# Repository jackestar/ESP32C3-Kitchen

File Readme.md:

<div align="center">
<h3>ESP32C3-Kitchen</h3>
<!--  -->
</div>

---

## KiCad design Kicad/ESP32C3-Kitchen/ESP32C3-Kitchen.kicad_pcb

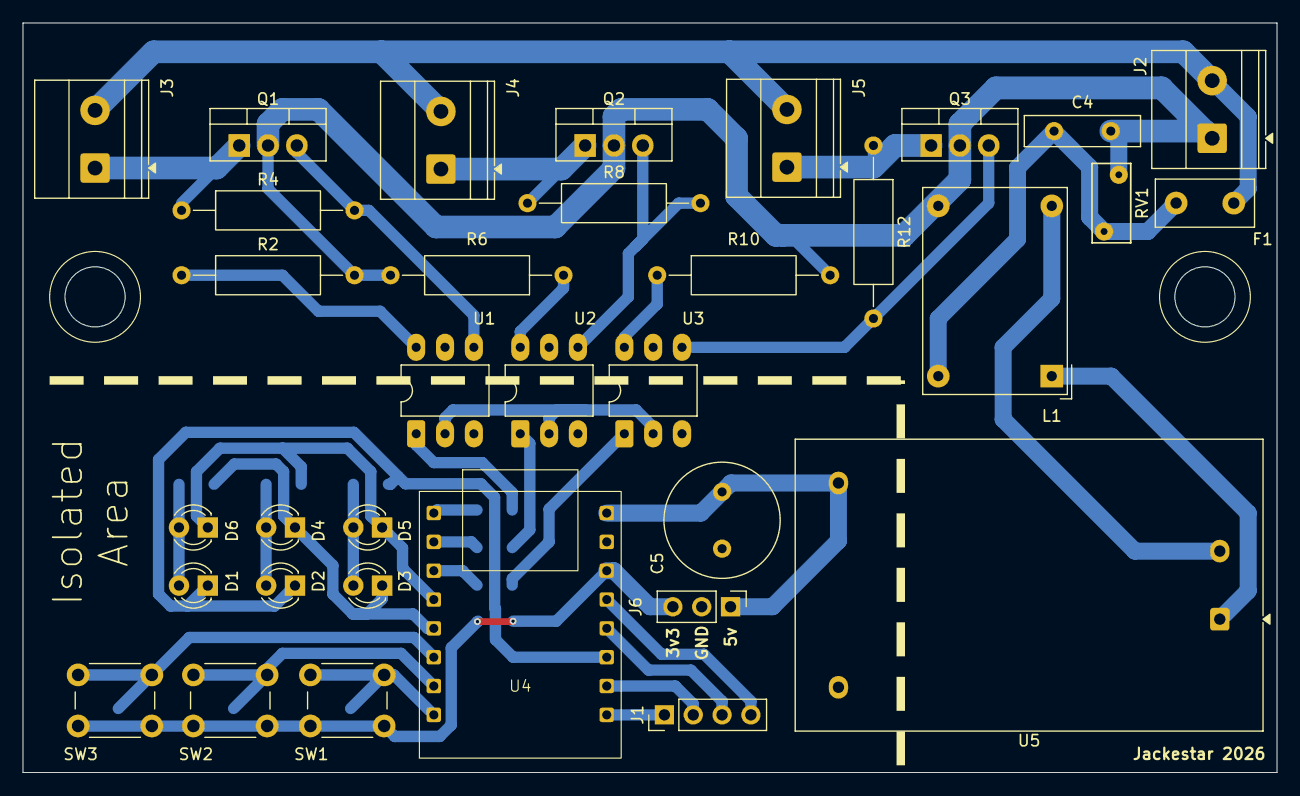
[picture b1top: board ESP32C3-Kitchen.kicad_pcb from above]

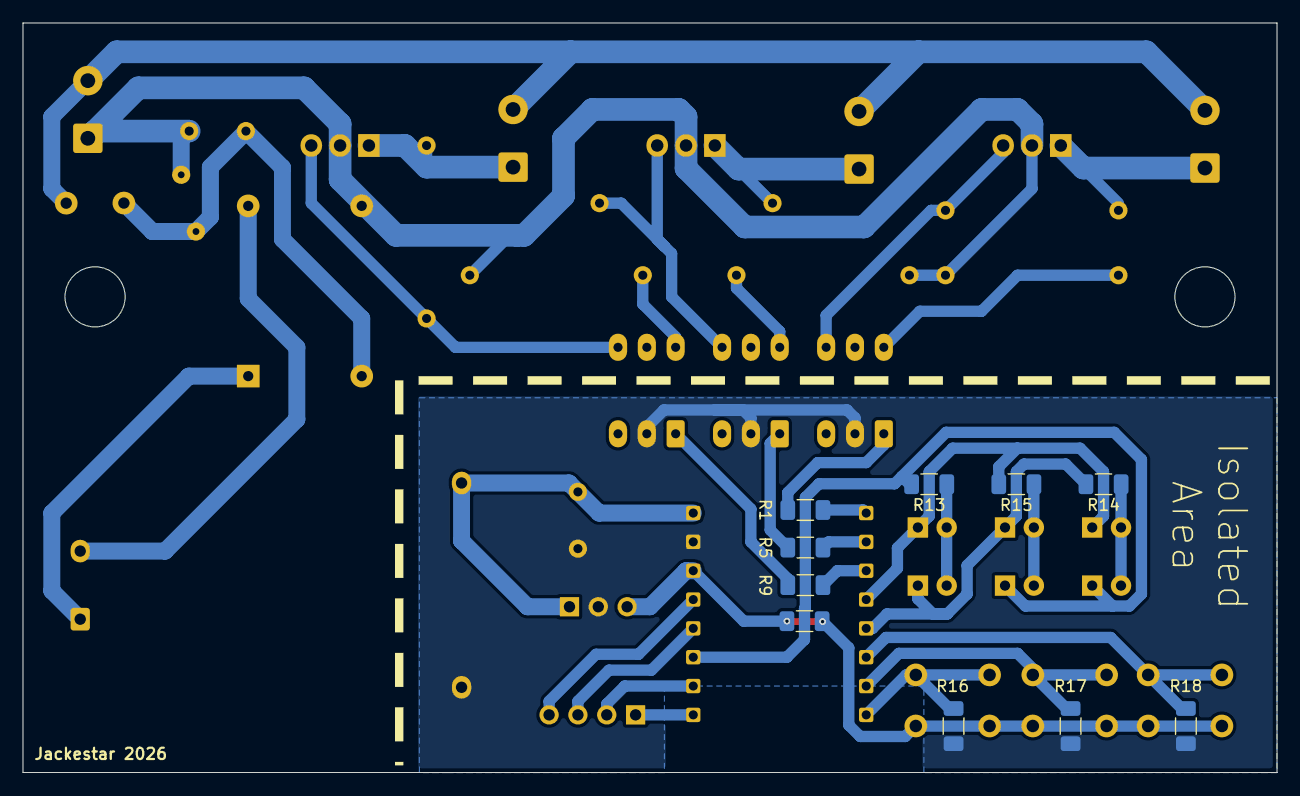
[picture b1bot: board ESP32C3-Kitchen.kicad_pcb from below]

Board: 2 copper layers, 110.5 x 66.0 mm, 43 parts (9 on the bottom side), 36 nets.

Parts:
C4: 0.1u; C_Disc_D10.0mm_W2.5mm_P5.00mm
C5: 220u; C_Radial_D10.0mm_H12.5mm_P5.00mm
D1, D2, D3, D4, D5, D6: LED; LED_D3.0mm
F1: 0.5; Fuse_Littelfuse_395Series
J1: Sense; PinHeader_1x04_P2.54mm_Vertical
J2, J3, J4, J5: Main AC; TerminalBlock_Phoenix_MKDS-1,5-2-5.08_1x02_P5.08mm_Horizont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
J6: Voltage Output; PinHeader_1x03_P2.54mm_Vertical
L1: 10u; Choke_Schaffner_RN212-04-12.5x18.0mm
Q1, Q2, Q3: BTA24-800B; TO-220-3_Vertical
R1, R5, R9: 150; R_1206_3216Metric_Pad1.30x1.75mm_HandSolder
R2, R6, R10: 360; R_Axial_DIN0309_L9.0mm_D3.2mm_P15.24mm_Horizontal
R4, R8, R12: 330; R_Axial_DIN0309_L9.0mm_D3.2mm_P15.24mm_Horizontal
R13, R14, R15: 220; R_1206_3216Metric_Pad1.30x1.75mm_HandSolder
R16, R17, R18: 1k; R_1206_3216Metric_Pad1.30x1.75mm_HandSolder
RV1: 560; RV_Disc_D7mm_W3.4mm_P5mm
SW1: Element 1; SW_PUSH_6mm
SW2: Element 2; SW_PUSH_6mm
SW3: Element 3; SW_PUSH_6mm
U1, U2, U3: MOC3041M; DIP-6_W7.62mm_LongPads
U4: ESP32C3-SM
U5: HLK-5M05; Converter_ACDC_Hi-Link_HLK-5Mxx

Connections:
+3V3: J6.3, SW1.1, SW2.1, SW3.1, U4.11 (3v3)
+5V: C5.1, J6.1, U4.9 (5v), U5.4 (+Vout)
CHP1: D1.1 (K), D2.1 (K), R13.2, U4.14 (GPIO2)
CHP2: D3.1 (K), D4.1 (K), R14.2, U4.5 (GPIO9)
CHP3: D5.1 (K), D6.1 (K), R15.2, U4.4 (GPIO8)
GNDD: C5.2, J6.2, R16.1, R17.1, R18.1, U1.2, U2.2, U3.2, U4.10 (GND), U5.3 (-Vout)
H1_B: R18.2, SW3.2, U4.6 (GPIO10)
H1_D: R1.1, U4.1 (GPIO5)
H1_S: J1.4, U4.12 (GPIO4)
H2_B: R17.2, SW2.2, U4.7 (GPIO20)
H2_D: R5.1, U4.2 (GPIO6)
H2_S: J1.3, U4.13 (GPIO3)
H3_B: R16.2, SW1.2, U4.8 (GPIO21)
H3_D: R9.1, U4.3 (GPIO7)
H3_S: J1.2, U4.15 (GPIO1)
LINE A: C4.2, J2.1, L1.4, Q1.2 (A2), Q2.2 (A2), Q3.2 (A2), R2.2, R6.2, R10.2, RV1.2
LINE B: F1.1, J2.2, J3.2, J4.2, J5.2
unnamed: C4.1, F1.2, L1.2, RV1.1
unnamed: D1.2 (A), D6.2 (A), R14.1
unnamed: D2.2 (A), D4.2 (A), R15.1
unnamed: D3.2 (A), D5.2 (A), R13.1
unnamed: J3.1, Q1.1 (A1), R4.1
unnamed: J4.1, Q2.1 (A1), R8.1
unnamed: J5.1, Q3.1 (A1), R12.1
unnamed: Q1.3 (G), R4.2, U1.4
unnamed: Q2.3 (G), R8.2, U2.4
unnamed: Q3.3 (G), R12.2, U3.4
unnamed: R1.2, U1.1
unnamed: R2.1, U1.6
unnamed: R5.2, U2.1
unnamed: R6.1, U2.6
unnamed: R9.2, U3.1
unnamed: R10.1, U3.6
unnamed: L1.1, U5.1 (AC/L)
unnamed: L1.3, U5.2 (AC/N)
V_Sens: J1.1, U4.16 (GPIO0)
